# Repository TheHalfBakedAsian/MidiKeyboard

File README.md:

# MidiKeyboard
The midikeyboard starter project taken down a notch. Designed with already owned parts in mind and large forgiving pads.

the design is very wide, simply due to the pads demanding it but I am able to squeeze the height of it down a tad bit. The overall model is inspired by the starter but I took a twist to save costs and make the project more affordable on my end because I own many of the substitutes like the full cherry MX switches over low profiles and Xiao over Wave. 
This all lets me end up with a little but janky but fun design like this.

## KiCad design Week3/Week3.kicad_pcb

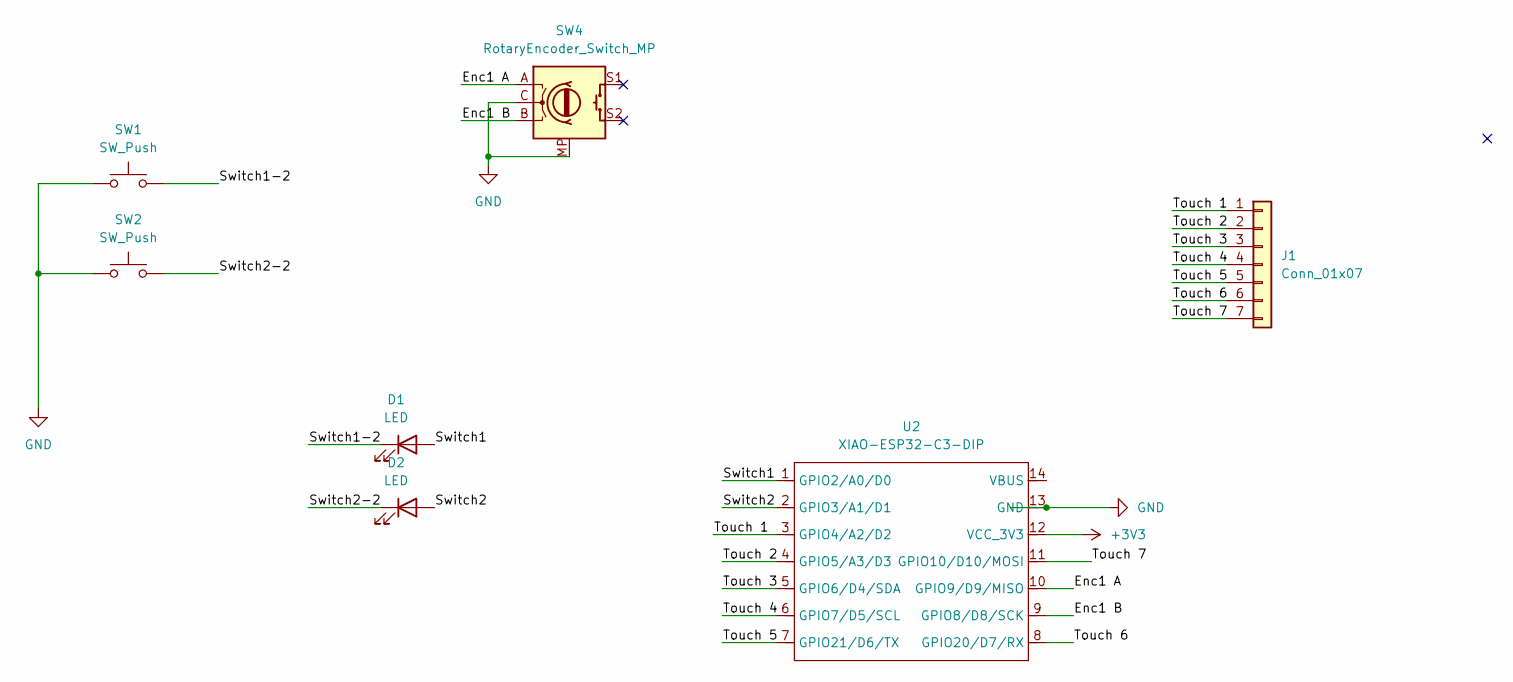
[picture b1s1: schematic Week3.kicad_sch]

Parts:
D1, D2: LED; Untitled
J1: Conn_01x07; Capictive Keys Midi
SW1, SW2: SW_Push; SW_Cherry_MX_1.00u_PCB
SW4: RotaryEncoder_Switch_MP; RotaryEncoder_Alps_EC11E-Switch_Vertical_H20mm
U2: XIAO-ESP32-C3-DIP; XIAO-ESP32C3-DIP

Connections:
+3V3: U2.12 (VCC_3V3)
/Enc1 A: SW4.A, U2.10 (GPIO9/D9/MISO)
/Enc1 B: SW4.B, U2.9 (GPIO8/D8/SCK)
/Switch1: D1.2 (A), U2.1 (GPIO2/A0/D0)
/Switch1-2: D1.1 (K), SW1.2
/Switch2: D2.2 (A), U2.2 (GPIO3/A1/D1)
/Switch2-2: D2.1 (K), SW2.2
/Touch 1: J1.1, U2.3 (GPIO4/A2/D2)
/Touch 2: J1.2, U2.4 (GPIO5/A3/D3)
/Touch 3: J1.3, U2.5 (GPIO6/D4/SDA)
/Touch 4: J1.4, U2.6 (GPIO7/D5/SCL)
/Touch 5: J1.5, U2.7 (GPIO21/D6/TX)
/Touch 6: J1.6, U2.8 (GPIO20/D7/RX)
/Touch 7: J1.7, U2.11 (GPIO10/D10/MOSI)
GND: SW1.1, SW2.1, SW4.C, SW4.MP, U2.13 (GND)

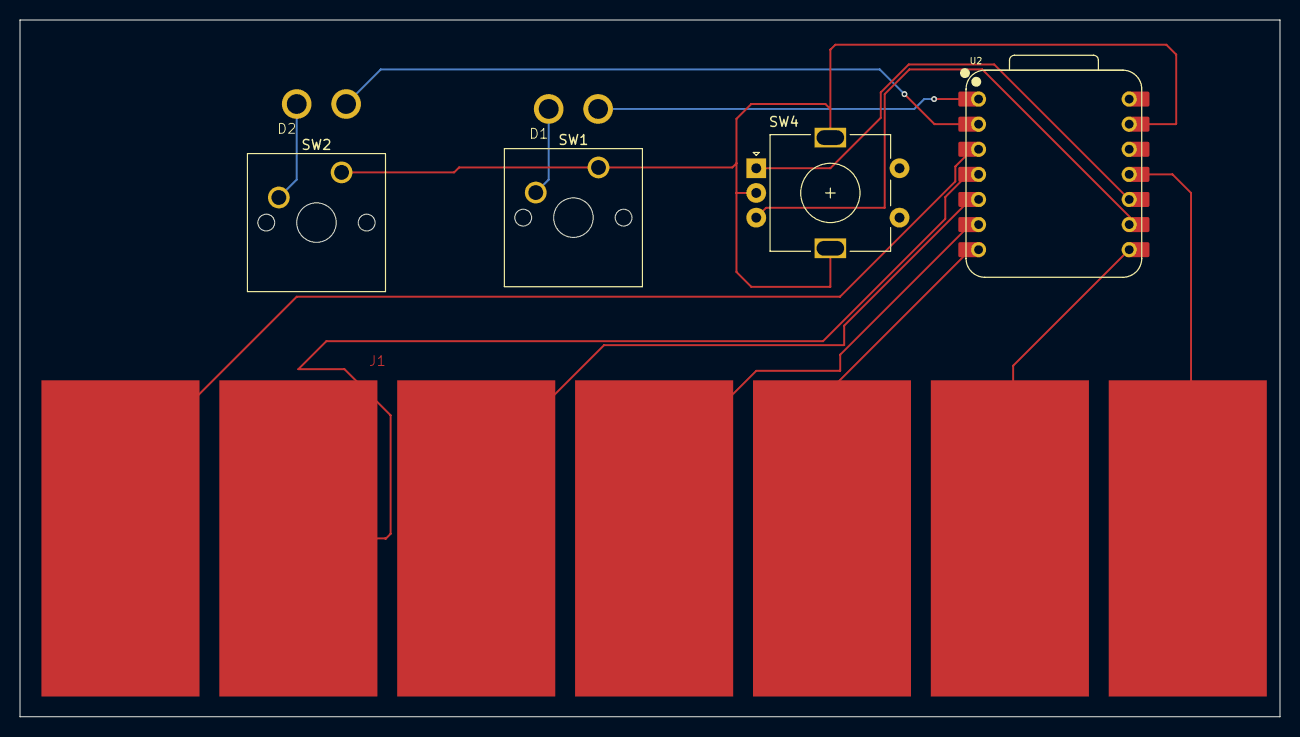
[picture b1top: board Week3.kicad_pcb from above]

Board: 2 copper layers, 127.5 x 70.5 mm, 7 parts (0 on the bottom side), 14 nets.

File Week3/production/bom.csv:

Designator,Footprint,Quantity,Value,LCSC Part #
"D1, D2",Untitled,2,LED,
J1,Capictive Keys Midi,1,Conn_01x07,
"SW1, SW2",SW_Cherry_MX_1.00u_PCB,2,SW_Push,
SW4,RotaryEncoder_Alps_EC11E-Switch_Vertical_H20mm,1,RotaryEncoder_Switch_MP,
U2,XIAO-ESP32C3-DIP,1,XIAO-ESP32-C3-DIP,
